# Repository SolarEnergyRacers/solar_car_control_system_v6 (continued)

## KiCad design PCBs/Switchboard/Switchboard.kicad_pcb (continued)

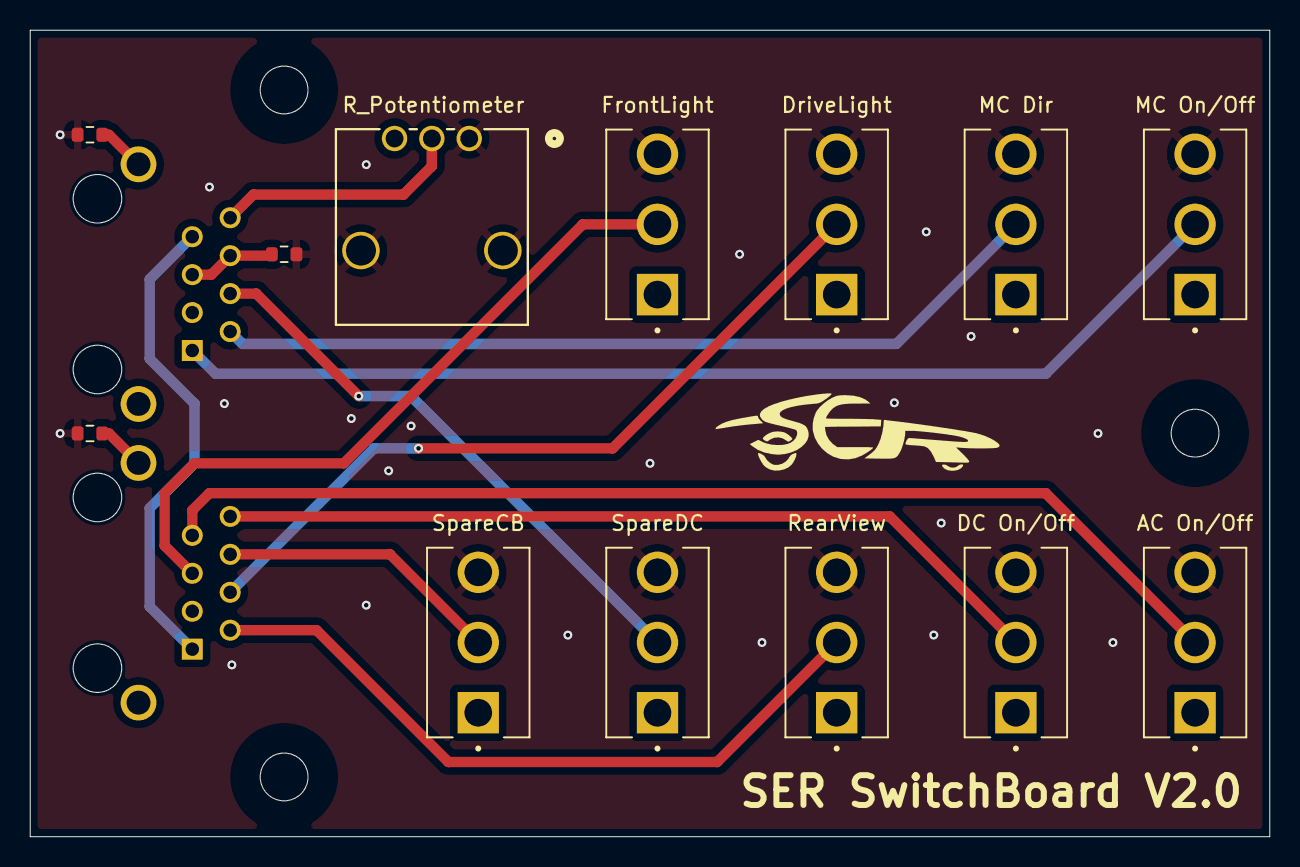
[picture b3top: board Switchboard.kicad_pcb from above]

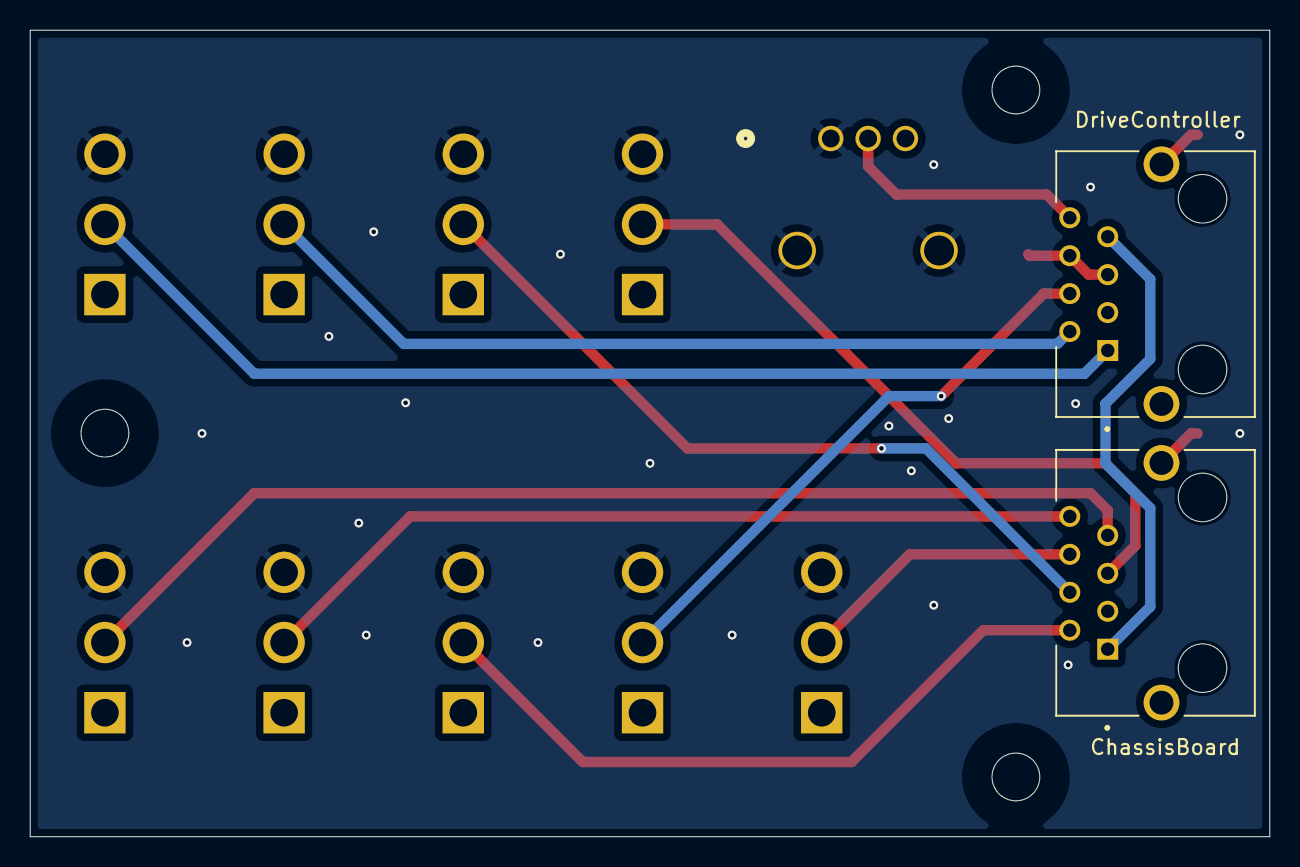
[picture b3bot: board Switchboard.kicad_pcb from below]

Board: 4 copper layers, 83.0 x 54.0 mm, 19 parts (2 on the bottom side), 16 nets.

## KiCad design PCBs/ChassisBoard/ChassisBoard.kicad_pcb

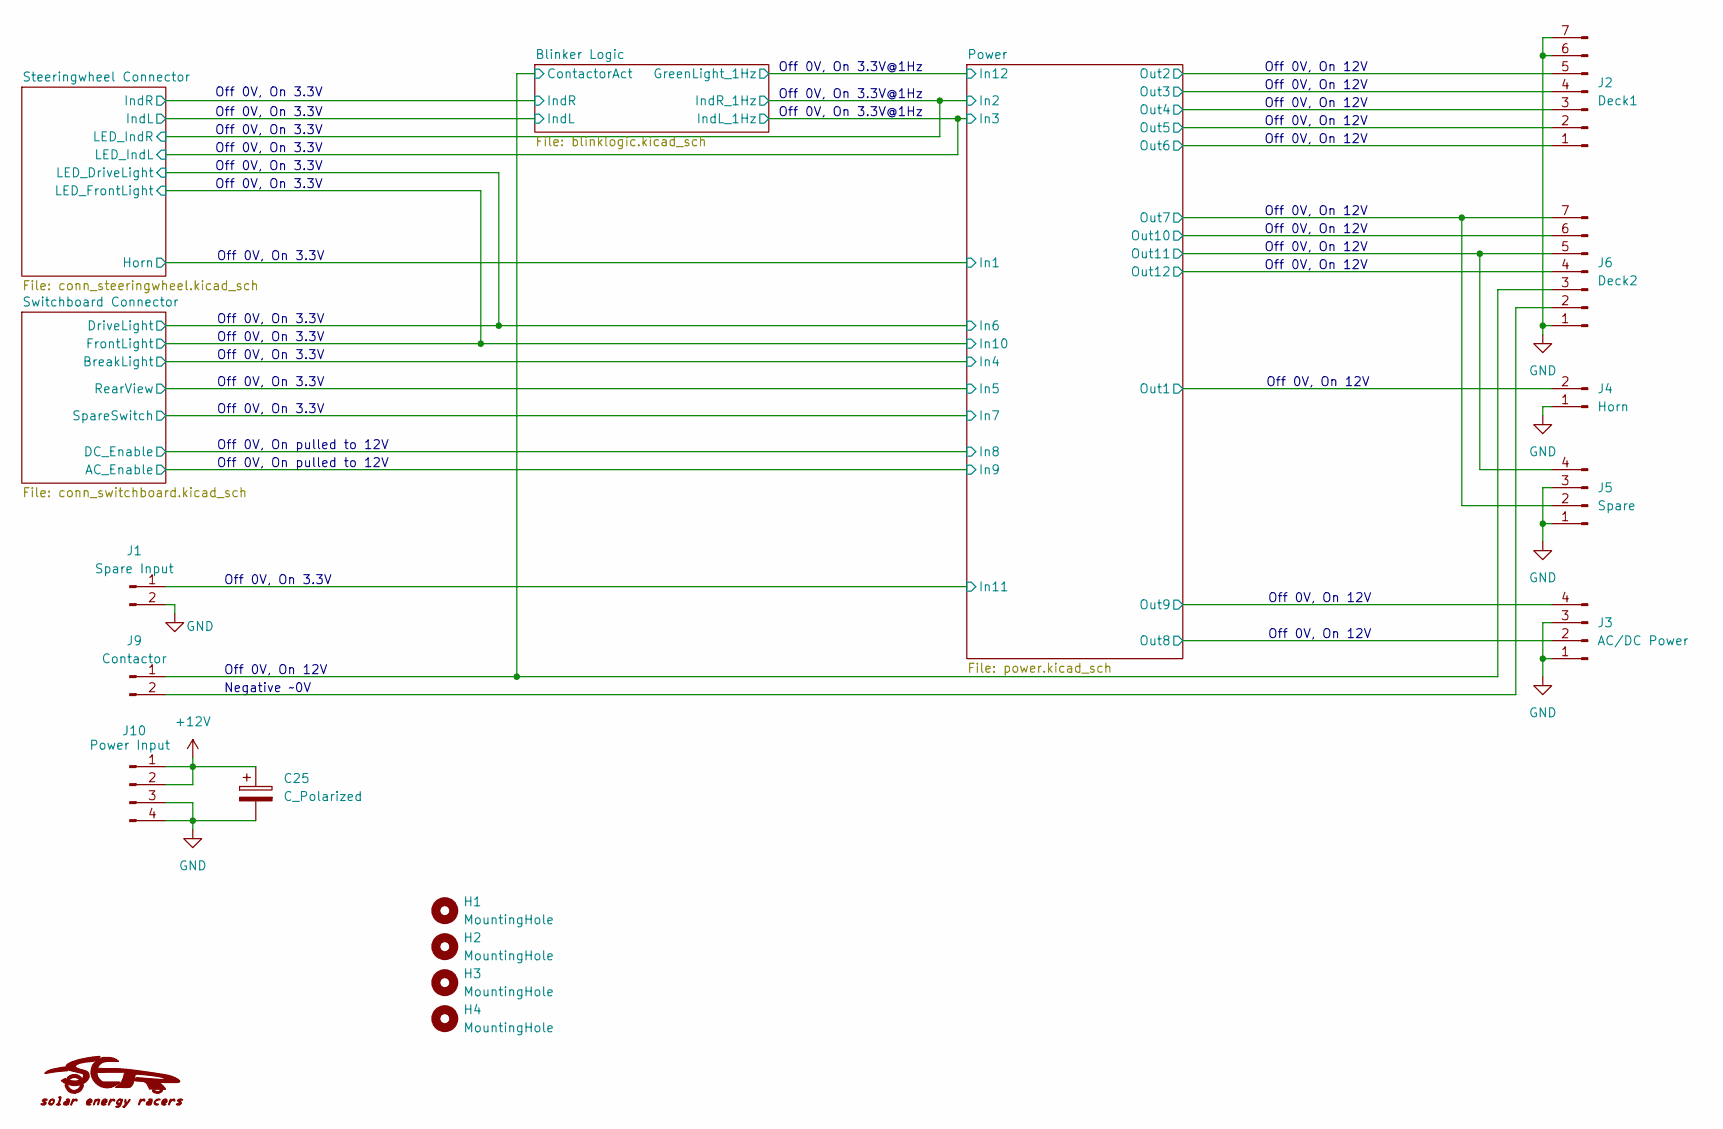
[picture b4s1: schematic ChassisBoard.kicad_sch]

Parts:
C25: C_Polarized; CP_Radial_D8.0mm_P5.00mm
H1, H2, H3, H4: MountingHole; MountingHole_3.2mm_M3_No_Copper
J1: Spare Input; PhoenixContact_MCV_1,5_2-G-3.5_1x02_P3.50mm_Vertical
J2: Deck1; PhoenixContact_MCV_1,5_7-G-3.5_1x07_P3.50mm_Vertical
J3: AC/DC Power; PhoenixContact_MCV_1,5_4-G-3.5_1x04_P3.50mm_Vertical
J4: Horn; PhoenixContact_MCV_1,5_2-G-3.5_1x02_P3.50mm_Vertical
J5: Spare; PhoenixContact_MCV_1,5_4-G-3.5_1x04_P3.50mm_Vertical
J6: Deck2; PhoenixContact_MCV_1,5_7-G-3.5_1x07_P3.50mm_Vertical
J9: Contactor; PhoenixContact_MCV_1,5_2-G-3.5_1x02_P3.50mm_Vertical
J10: Power Input; PhoenixContact_MCV_1,5_4-G-3.5_1x04_P3.50mm_Vertical

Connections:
+12V: C25.1, J10.1, J10.2; also elsewhere on the board
/Blinker Logic/ContactorAct: J6.3, J9.1; also elsewhere on the board
/Power/In11: J1.1; also elsewhere on the board
/Power/Out1: J4.2; also elsewhere on the board
/Power/Out2: J2.5; also elsewhere on the board
/Power/Out3: J2.4; also elsewhere on the board
/Power/Out4: J2.3; also elsewhere on the board
/Power/Out5: J2.2; also elsewhere on the board
/Power/Out6: J2.1; also elsewhere on the board
/Power/Out7: J5.2, J6.7; also elsewhere on the board
/Power/Out8: J3.2; also elsewhere on the board
/Power/Out9: J3.4; also elsewhere on the board
/Power/Out10: J6.6; also elsewhere on the board
/Power/Out11: J5.4, J6.5; also elsewhere on the board
/Power/Out12: J6.4; also elsewhere on the board
GND: C25.2, J1.2, J2.6, J2.7, J3.1, J3.3, J4.1, J5.1, J5.3, J6.1, J10.3, J10.4; also elsewhere on the board
unnamed: J6.2, J9.2

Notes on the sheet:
Off 0V, On 3.3V
Off 0V, On pulled to 12V
Off 0V, On 12V
Off 0V, On 3.3V@1Hz
Negative ~0V

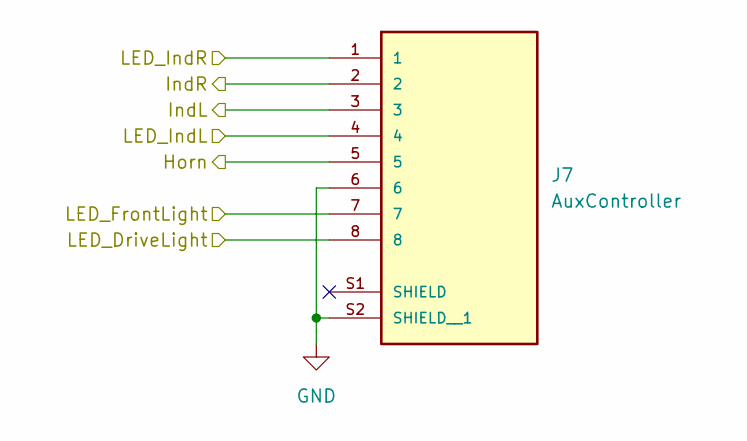
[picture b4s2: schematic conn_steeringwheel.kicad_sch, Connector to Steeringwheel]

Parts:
J7: AuxController; CUI_CRJ027-1-TH; PARTREV 1.0

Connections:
/Blinker Logic/IndL: J7.3; also elsewhere on the board
/Blinker Logic/IndL_1Hz: J7.4; also elsewhere on the board
/Blinker Logic/IndR: J7.2; also elsewhere on the board
/Blinker Logic/IndR_1Hz: J7.1; also elsewhere on the board
/Power/In1: J7.5; also elsewhere on the board
/Power/In6: J7.8; also elsewhere on the board
/Power/In10: J7.7; also elsewhere on the board
GND: J7.6, J7.S2 (SHIELD__1); also elsewhere on the board

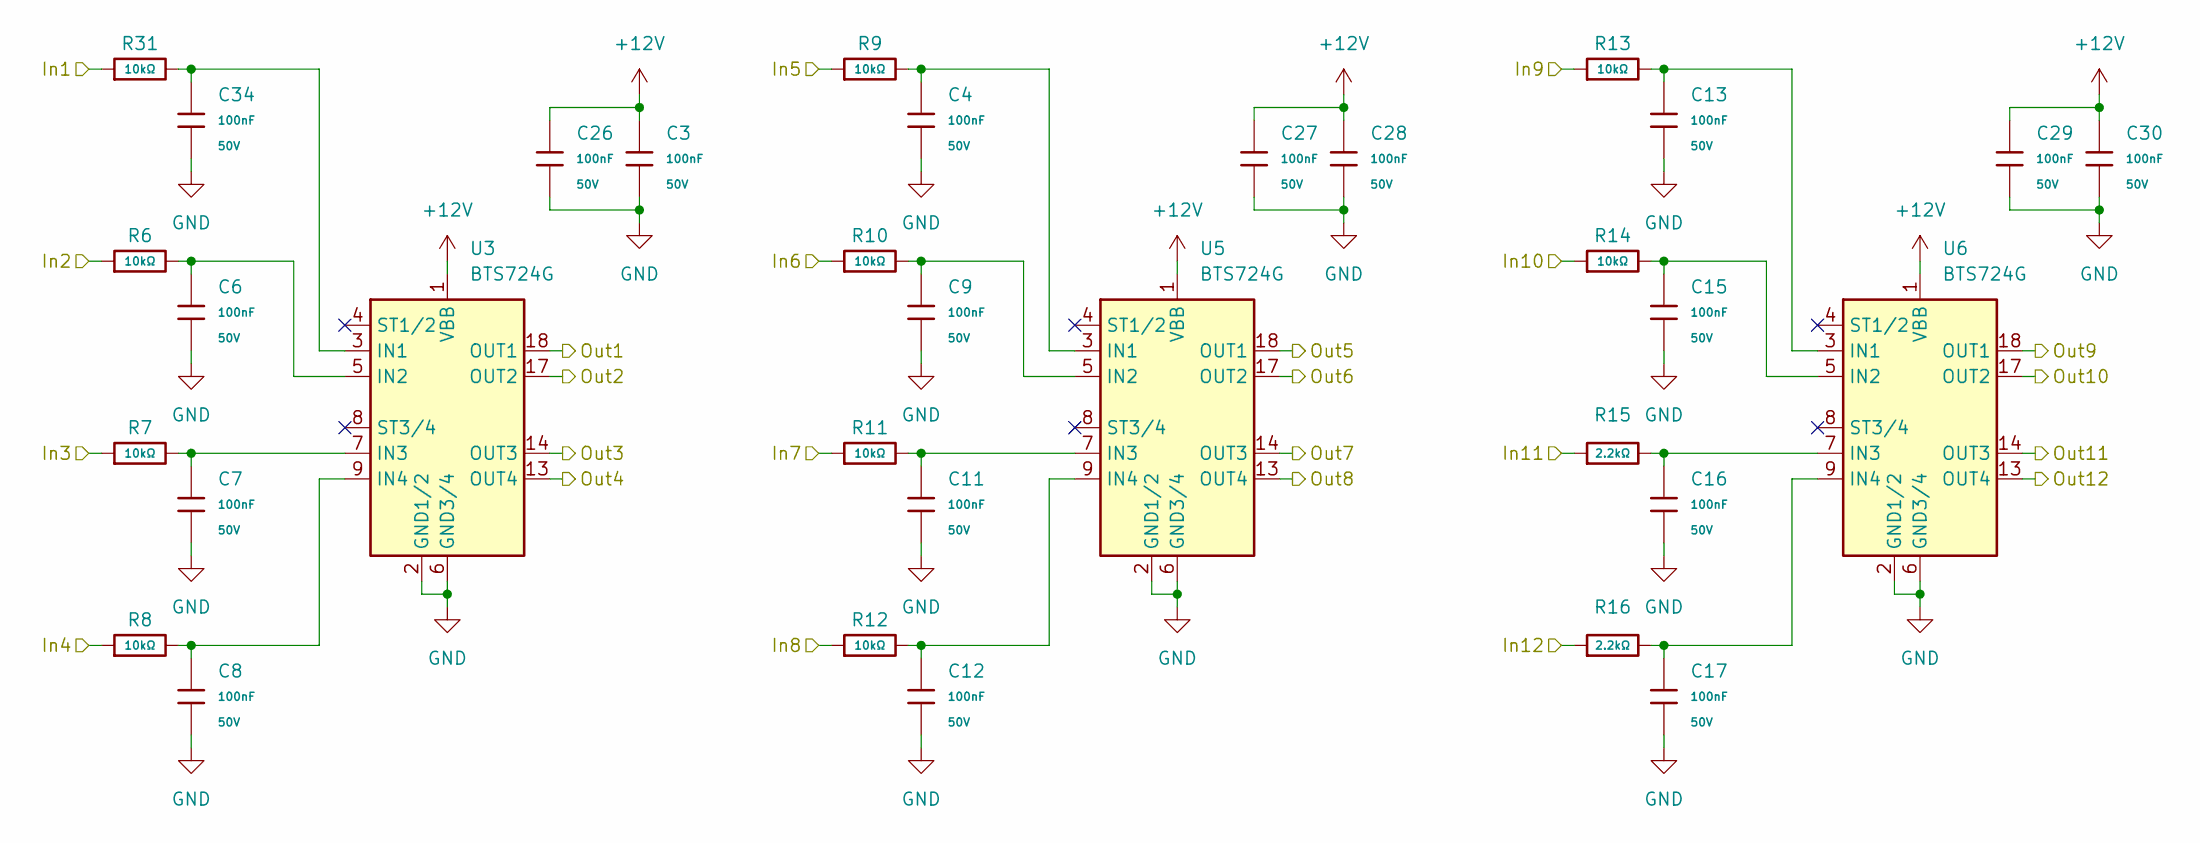
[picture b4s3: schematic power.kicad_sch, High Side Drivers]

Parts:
C3, C4, C6, C7, C8, C9, C11, C12, C13, C15, C16, C17, C26, C27, C28, C29, C30, C34: 100nF; C_0603; Voltage Rated 50V; Tolerance ±10%; Part CC0603KRX7R9BB104; LCSC C14663
R6, R7, R8, R9, R10, R11, R12, R13, R14, R31: 10kΩ; R_0603; Overload Voltage (Max) 75V; Tolerance ±1%; Part 0603WAF1002T5E; LCSC C25804
R15, R16: 2.2kΩ; R_0603; Overload Voltage (Max) 75V; Tolerance ±1%; Part 0603WAF2201T5E; LCSC C4190
U3, U5, U6: BTS724G; Infineon_SOIC-20W_7.6x12.8mm_P1.27mm

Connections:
+12V: C3.1, C26.1, C27.1, C28.1, C29.1, C30.1, U3.1 (VBB), U3.10 (VBB), U3.11 (VBB), U3.12 (VBB), U3.15 (VBB), U3.16 (VBB), U3.19 (VBB), U3.20 (VBB), U5.1 (VBB), U5.10 (VBB), U5.11 (VBB), U5.12 (VBB), U5.15 (VBB), U5.16 (VBB), U5.19 (VBB), U5.20 (VBB), U6.1 (VBB), U6.10 (VBB), U6.11 (VBB), U6.12 (VBB), U6.15 (VBB), U6.16 (VBB), U6.19 (VBB), U6.20 (VBB); also elsewhere on the board
/Blinker Logic/GreenLight_1Hz: R16.1; also elsewhere on the board
/Blinker Logic/IndL_1Hz: R7.1; also elsewhere on the board
/Blinker Logic/IndR_1Hz: R6.1; also elsewhere on the board
/Power/In1: R31.1; also elsewhere on the board
/Power/In4: R8.1; also elsewhere on the board
/Power/In5: R9.1; also elsewhere on the board
/Power/In6: R10.1; also elsewhere on the board
/Power/In7: R11.1; also elsewhere on the board
/Power/In8: R12.1; also elsewhere on the board
/Power/In9: R13.1; also elsewhere on the board
/Power/In10: R14.1; also elsewhere on the board
/Power/In11: R15.1; also elsewhere on the board
/Power/Out1: U3.18 (OUT1); also elsewhere on the board
/Power/Out2: U3.17 (OUT2); also elsewhere on the board
/Power/Out3: U3.14 (OUT3); also elsewhere on the board
/Power/Out4: U3.13 (OUT4); also elsewhere on the board
/Power/Out5: U5.18 (OUT1); also elsewhere on the board
/Power/Out6: U5.17 (OUT2); also elsewhere on the board
/Power/Out7: U5.14 (OUT3); also elsewhere on the board
/Power/Out8: U5.13 (OUT4); also elsewhere on the board
/Power/Out9: U6.18 (OUT1); also elsewhere on the board
/Power/Out10: U6.17 (OUT2); also elsewhere on the board
/Power/Out11: U6.14 (OUT3); also elsewhere on the board
/Power/Out12: U6.13 (OUT4); also elsewhere on the board
GND: C3.2, C4.2, C6.2, C7.2, C8.2, C9.2, C11.2, C12.2, C13.2, C15.2, C16.2, C17.2, C26.2, C27.2, C28.2, C29.2, C30.2, C34.2, U3.2 (GND1/2), U3.6 (GND3/4), U5.2 (GND1/2), U5.6 (GND3/4), U6.2 (GND1/2), U6.6 (GND3/4); also elsewhere on the board
unnamed: C34.1, R31.2, U3.3 (IN1)
unnamed: C6.1, R6.2, U3.5 (IN2)
unnamed: C7.1, R7.2, U3.7 (IN3)
unnamed: C8.1, R8.2, U3.9 (IN4)
unnamed: C4.1, R9.2, U5.3 (IN1)
unnamed: C9.1, R10.2, U5.5 (IN2)
unnamed: C11.1, R11.2, U5.7 (IN3)
unnamed: C12.1, R12.2, U5.9 (IN4)
unnamed: C13.1, R13.2, U6.3 (IN1)
unnamed: C15.1, R14.2, U6.5 (IN2)
unnamed: C16.1, R15.2, U6.7 (IN3)
unnamed: C17.1, R16.2, U6.9 (IN4)

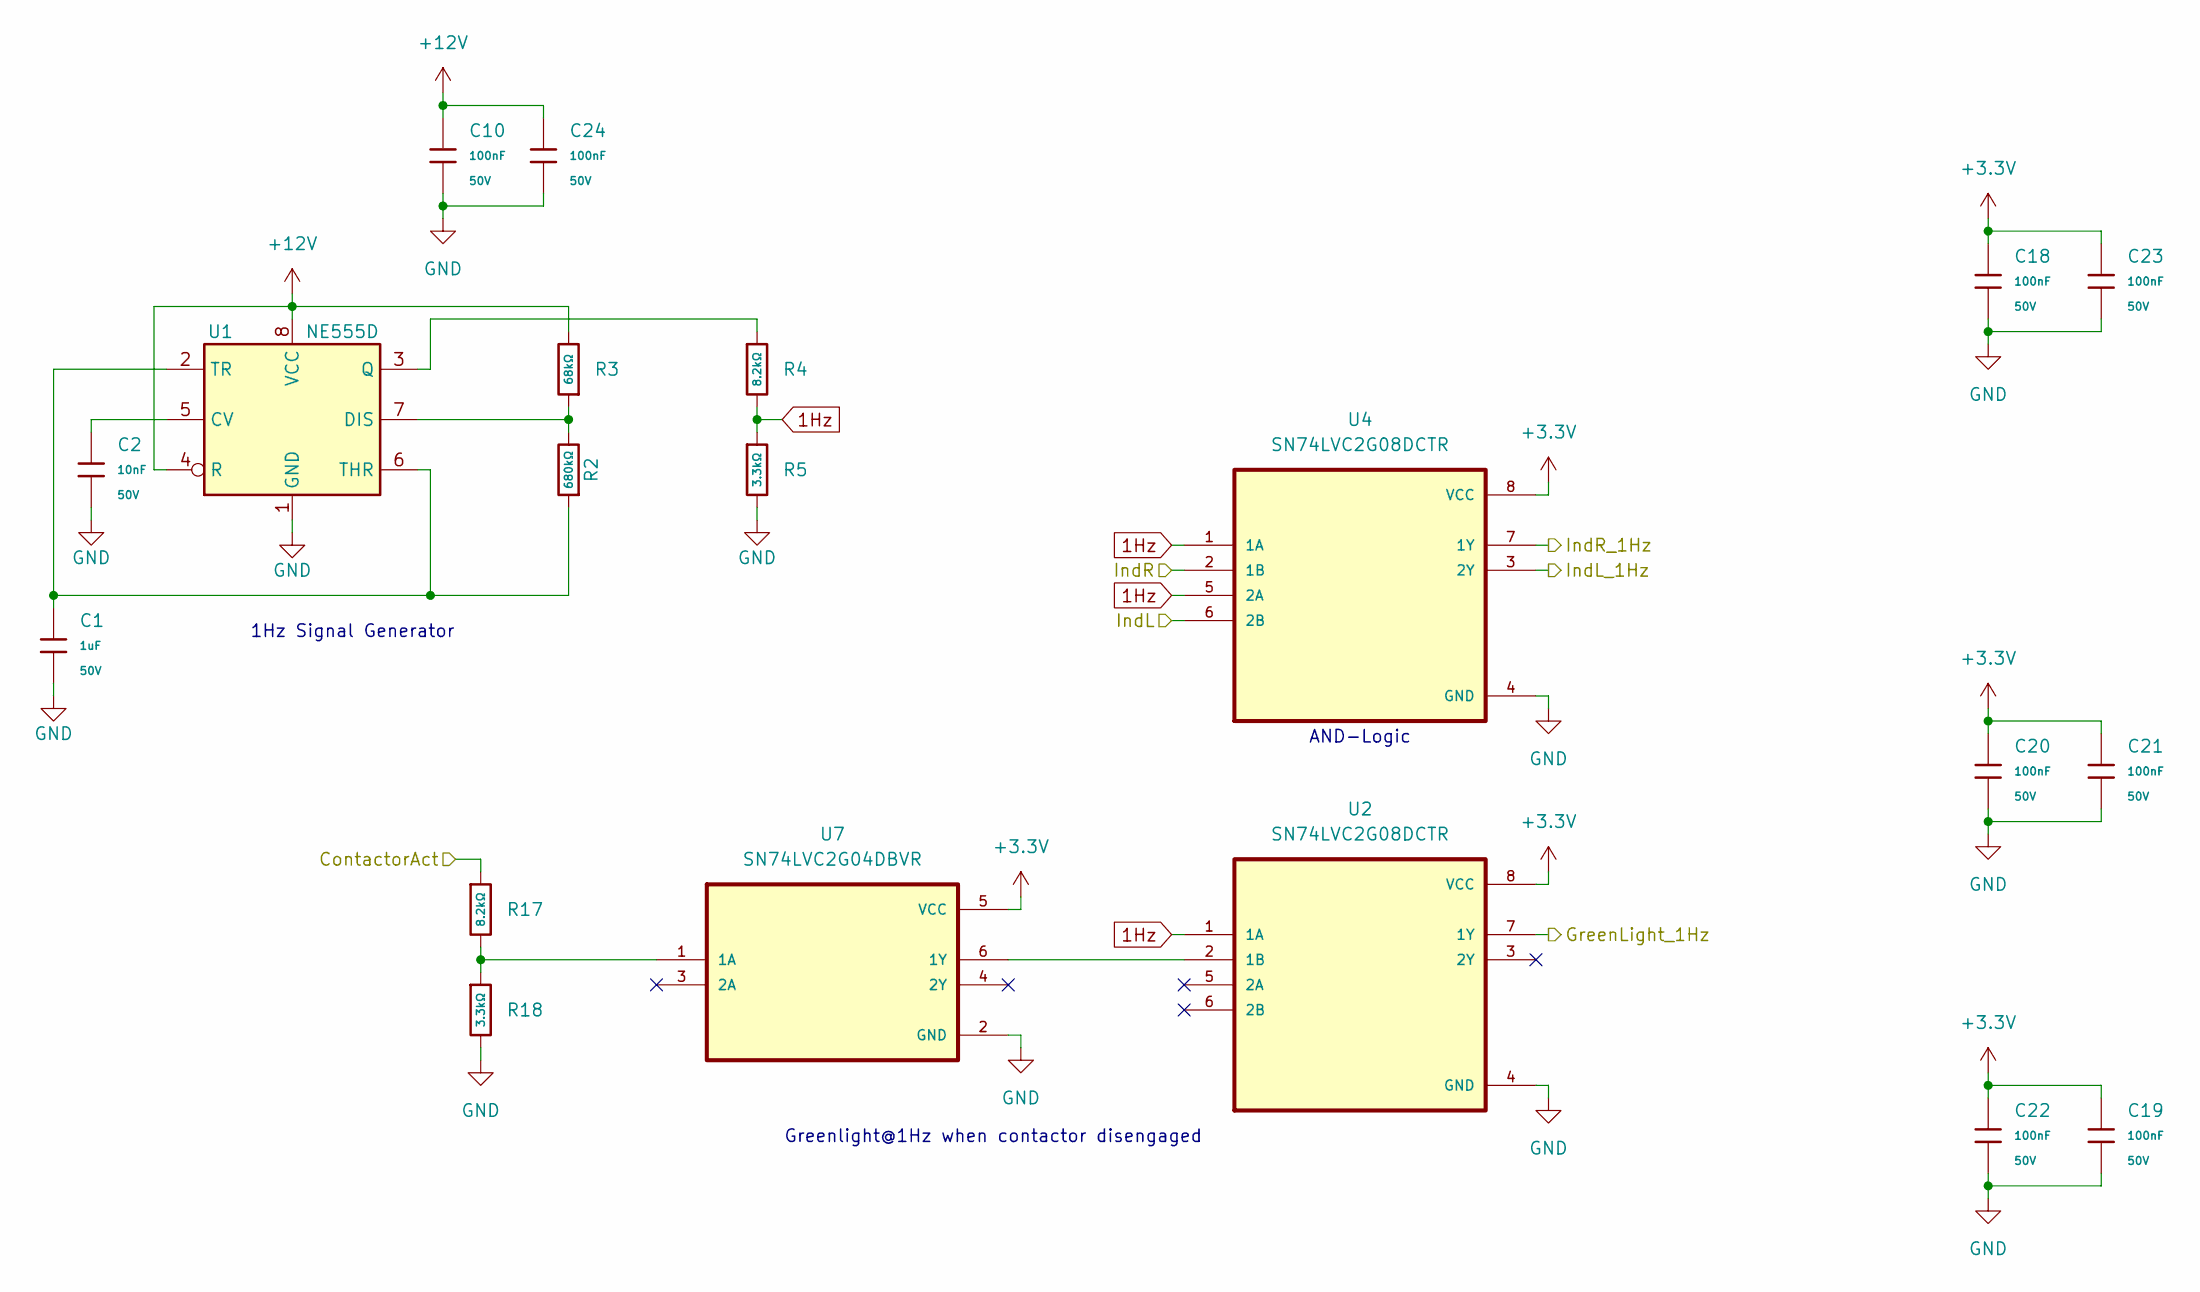
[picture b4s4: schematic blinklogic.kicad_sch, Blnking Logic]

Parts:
C1: 1uF; C_0603; Voltage Rated 50V; Tolerance ±10%; Part CL10A105KB8NNNC; LCSC C15849
C2: 10nF; C_0603; Voltage Rated 50V; Tolerance ±10%; Part 0603B103K500NT; LCSC C57112
C10, C18, C19, C20, C21, C22, C23, C24: 100nF; C_0603; Voltage Rated 50V; Tolerance ±10%; Part CC0603KRX7R9BB104; LCSC C14663
R2: 680kΩ; R_0603; Overload Voltage (Max) 75V; Tolerance ±1%; Part 0603WAF6803T5E; LCSC C25822
R3: 68kΩ; R_0603; Overload Voltage (Max) 75V; Tolerance ±1%; Part 0603WAF6802T5E; LCSC C23231
R4, R17: 8.2kΩ; R_0603; Overload Voltage (Max) 75V; Tolerance ±1%; Part 0603WAF8201T5E; LCSC C25981
R5, R18: 3.3kΩ; R_0603; Overload Voltage (Max) 75V; Tolerance ±1%; Part 0603WAF3301T5E; LCSC C22978
U1: NE555D; SOIC-8_3.9x4.9mm_P1.27mm
U2, U4: SN74LVC2G08DCTR; VSSOP-8_2.3x2mm_P0.5mm_modified
U7: SN74LVC2G04DBVR; SOT-23-6

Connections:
1Hz: R4.2, R5.1, U2.1 (1A), U4.1 (1A), U4.5 (2A)
+3.3V: C18.1, C19.1, C20.1, C21.1, C22.1, C23.1, U2.8 (VCC), U4.8 (VCC), U7.5 (VCC); also elsewhere on the board
+12V: C10.1, C24.1, R3.2, U1.4 (R), U1.8 (VCC); also elsewhere on the board
/Blinker Logic/ContactorAct: R17.1; also elsewhere on the board
/Blinker Logic/GreenLight_1Hz: U2.7 (1Y); also elsewhere on the board
/Blinker Logic/IndL: U4.6 (2B); also elsewhere on the board
/Blinker Logic/IndL_1Hz: U4.3 (2Y); also elsewhere on the board
/Blinker Logic/IndR: U4.2 (1B); also elsewhere on the board
/Blinker Logic/IndR_1Hz: U4.7 (1Y); also elsewhere on the board
GND: C1.2, C2.2, C10.2, C18.2, C19.2, C20.2, C21.2, C22.2, C23.2, C24.2, R5.2, R18.2, U1.1 (GND), U2.4 (GND), U4.4 (GND), U7.2 (GND); also elsewhere on the board
unnamed: C2.1, U1.5 (CV)
unnamed: R2.2, R3.1, U1.7 (DIS)
unnamed: R4.1, U1.3 (Q)
unnamed: C1.1, R2.1, U1.2 (TR), U1.6 (THR)
unnamed: U2.2 (1B), U7.6 (1Y)
unnamed: R17.2, R18.1, U7.1 (1A)

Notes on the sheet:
1Hz Signal Generator
Greenlight@1Hz when contactor disengaged
AND-Logic

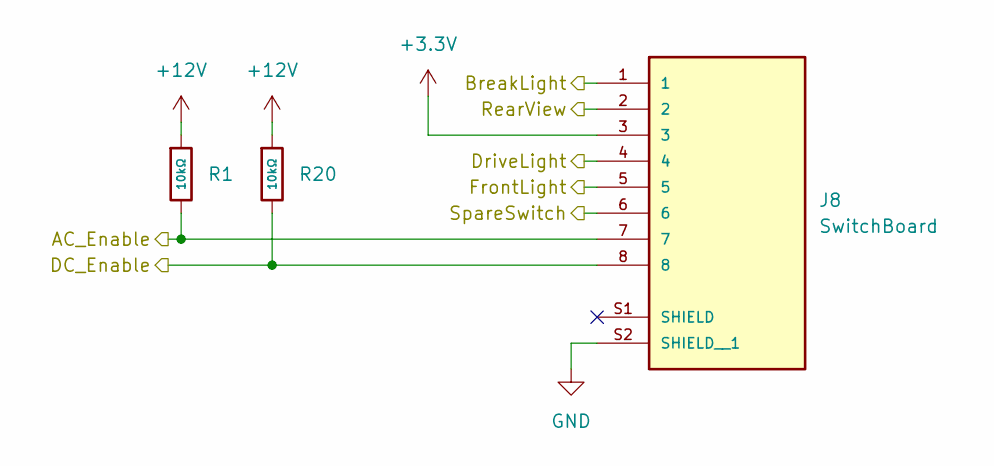
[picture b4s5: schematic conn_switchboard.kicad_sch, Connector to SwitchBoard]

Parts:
J8: SwitchBoard; CUI_CRJ027-1-TH; PARTREV 1.0
R1, R20: 10kΩ; R_0603; Overload Voltage (Max) 75V; Tolerance ±1%; Part 0603WAF1002T5E; LCSC C25804

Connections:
+3.3V: J8.3; also elsewhere on the board
+12V: R1.1, R20.1; also elsewhere on the board
/Power/In4: J8.1; also elsewhere on the board
/Power/In5: J8.2; also elsewhere on the board
/Power/In6: J8.4; also elsewhere on the board
/Power/In7: J8.6; also elsewhere on the board
/Power/In8: J8.8, R20.2; also elsewhere on the board
/Power/In9: J8.7, R1.2; also elsewhere on the board
/Power/In10: J8.5; also elsewhere on the board
GND: J8.S2 (SHIELD__1); also elsewhere on the board

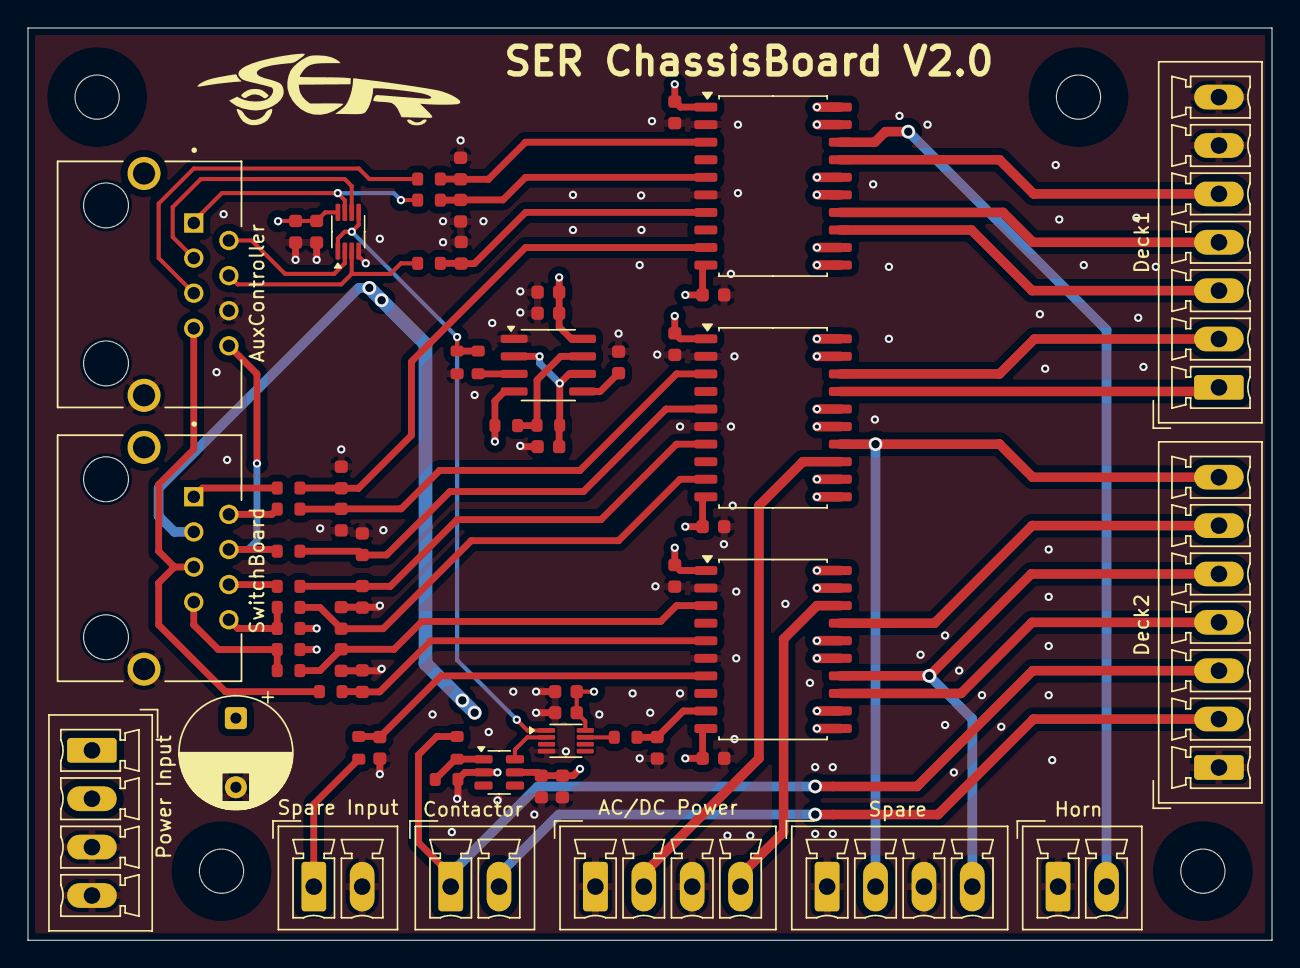
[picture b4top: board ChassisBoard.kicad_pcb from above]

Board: 4 copper layers, 90.0 x 66.0 mm, 70 parts (0 on the bottom side), 50 nets.

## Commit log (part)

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2025-11-17 initial init: Controllers, PCBs, docs, datasheets
2025-11-17 Update project description for SER v6 solar car
2026-01-04 Files for InnoSwitch added
2026-04-13 initial SER6 commit, AC-DC working together
2026-04-27 MPPT configuration files
    For SN136, SN139, SN140 with 130.2V
2026-05-03 working PWM, to fis: acc decc missmatch
2026-05-26 change break pedal logic, add ili9341 PCB picture, clean up
2026-05-27 PWM 1kHz, cleanup duplicate CanBusHandler
2026-05-27 clean up
2026-06-02 clean up, LLM analysis of code added
2026-06-02 speed up all tasks (now acc/decc < 1s)
2026-06-03 exclude MC CAN communication
2026-06-04 CAN optimizing, not full panic free
2026-06-07 test changes
2026-06-07 CAN: migrate to TWAI and harden critical AC/DC reliability
    - switch CANBus transport from arduino-CAN to ESP-IDF TWAI
    - add critical staleness watchdog for 0x650/0x660/0x661
    - add critical TX lane and sequence-gap detection
    - add overwrite/failure observability counters and retries
    - remove arduino-CAN deps and update analysis docs
2026-06-07 new can library
2026-06-08 cd card wo crashes but not mountingnew can library
2026-06-08 sd card working, logging works
2026-06-11 add fixed library files
2026-06-11 add possibility to print/tail files from sd-card to console
